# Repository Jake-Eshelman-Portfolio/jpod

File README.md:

# jPod Project Summary

## Goal
A handheld, music-only player about the size of an iPod Video. Stores 32–64GB of music, has a small screen with menus, a 4-way D-pad plus select, Bluetooth headphones, and a wired 3.5mm jack as backup.

## Core design
- **Brain:** ESP32-WROVER (original ESP32). It has classic Bluetooth for headphone audio, Wi-Fi, and 8MB of extra RAM for buffering.
- **Audio:** TI TLV320DAC3100 DAC with a built-in headphone amp, feeding a 3.5mm jack.
- **Storage:** microSD card.
- **Screen:** 2" ST7789 color display.
- **Power:** LiPo battery (1500–2500mAh), USB-C charging, battery-level chip.
- **Software:** Rust on ESP-IDF (`std`). Symphonia handles MP3/FLAC decoding and tags.

## Features
- **Local playback** from the SD card, browsing by artist and album.
- **Streaming** from Navidrome on the Pi over Wi-Fi. Away from home, it reaches the Pi through Tailscale Funnel, protected by a password and a secret token.
- **"Find similar":** pick a song, and the Pi asks Last.fm for similar tracks, then plays any matches from the library or adds the rest to a wishlist.
- **Firmware updates** over Wi-Fi.

## Decisions
- Start with one ESP32. Add a second one for Bluetooth only if streaming over Wi-Fi while playing through Bluetooth stutters.
- Use a 3.5mm jack instead of USB-C headphones.
- Leave LTE for v2, but reserve a spare UART and power header on v1.
- Skip Spotify's API, since it's too locked down now. Use Last.fm instead.

## Plan
1. **Prototype on a breadboard** with a dev kit and breakouts, powered over USB.
2. **Write the software:** playback, UI, Bluetooth, streaming, "find similar".
3. **Design the custom PCB in KiCad** using the same chips.
4. **Order parts.** Separate BOM for schematic based final build and the prototype that will be used to create a test bench.

## Prepare an SD Card (Linux/WSL)
1. Insert the card and inspect disks and partitions:
	```bash
	lsblk -o NAME,PATH,TRAN,RM,SIZE,MODEL,TYPE,FSTYPE,MOUNTPOINTS
	```
2. Identify the removable USB **disk** by model and capacity. Use the whole-disk path (for example, `/dev/sde`), not a partition path such as `/dev/sde1`. The script erases the whole selected disk and creates one MBR/FAT32 partition; Linux sees the USB reader and cannot prove what media is inserted.
3. Ensure `mp3_samples/` contains at least one MP3, then run from the repository root, substituting the verified disk path:
	```bash
	sudo ./helper_scripts/partition_sd_card.sh /dev/sde
	```
4. Check the script's printed model, capacity, and partition list carefully. Continue only if they match the SD card you intend to erase, then type the exact confirmation it requests (device path and size in bytes).

5. To check the music on card:
    - sudo mkdir -p /mnt/jpod-card
    - sudo mount /dev/sde1 /mnt/jpod-card
    - ls /mnt/jpod-card/mp3_samples
    - sudo umount /mnt/jpod-card

The script refuses mounted or otherwise in-use disks. Install its Linux tools if needed with `sudo apt install util-linux fdisk parted dosfstools udev coreutils findutils gawk` (`parted` provides `partprobe`).

## Watch out for
- Wi-Fi and Bluetooth share one radio on the ESP32, so buffer streams aggressively.
- The DAC needs its own 1.8V supply on the custom board.
- The CP2102N USB chip has a long lead time, so buy it early or find a good substitution.

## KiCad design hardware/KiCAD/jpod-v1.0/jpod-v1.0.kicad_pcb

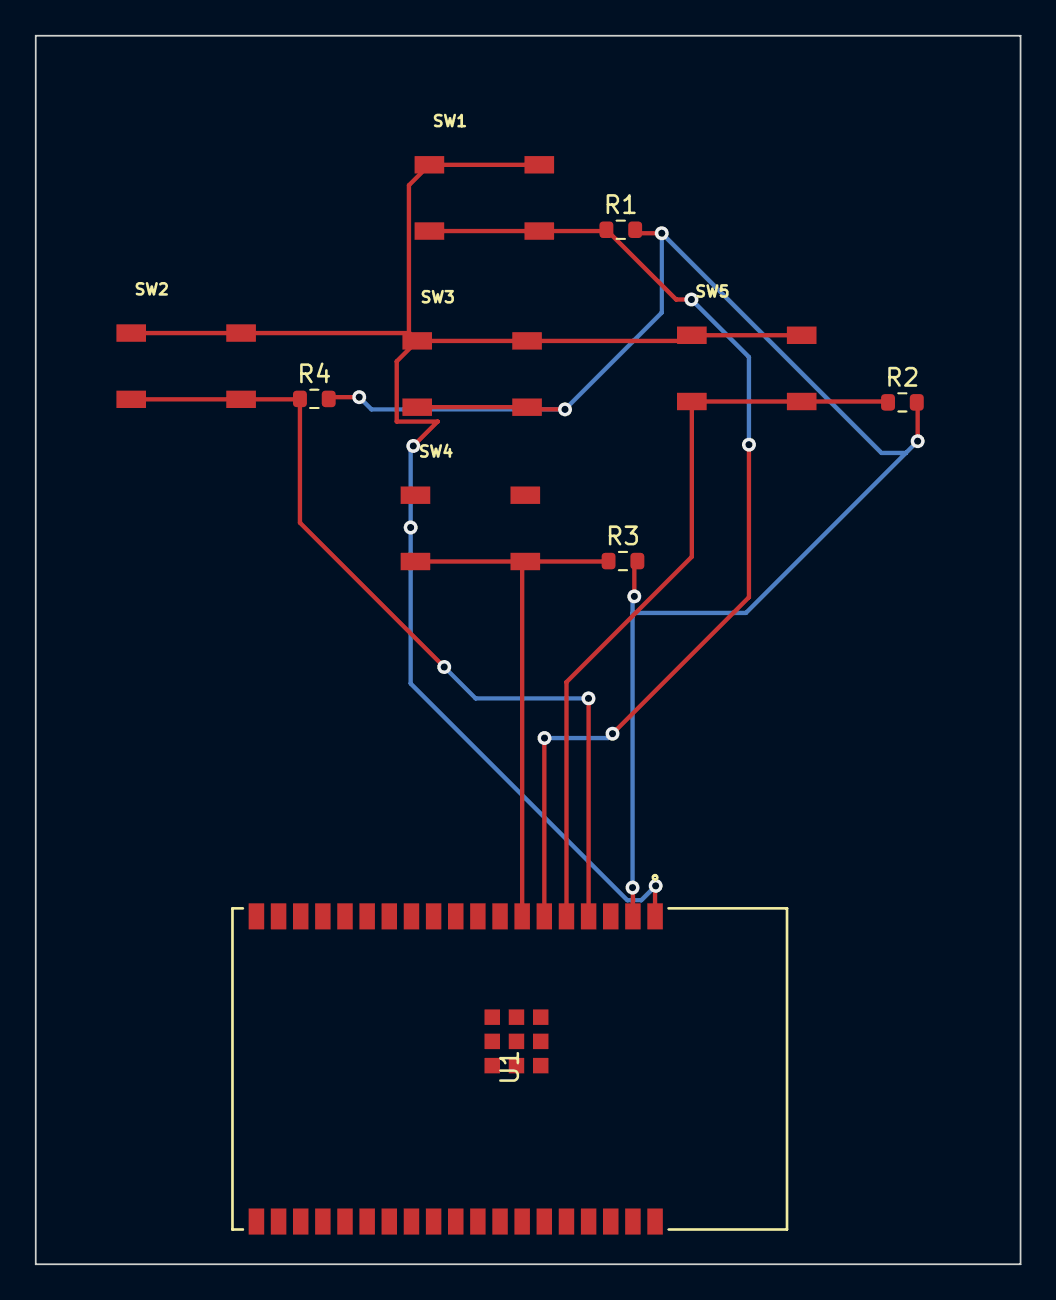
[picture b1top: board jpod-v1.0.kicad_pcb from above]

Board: 2 copper layers, 56.5 x 70.4 mm, 10 parts (0 on the bottom side), 6 nets.

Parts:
R1, R2, R3, R4: 10K; R_0603_1608Metric
SW1, SW2, SW3, SW4, SW5: TL3342F160QG_TR; SW_TL3342F160QG_TR
U1: ESP32-WROVER-E-N16R8; ESP32-WROVER-E_EXP

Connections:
/3V3: R1.2, R2.2, R3.2, R4.2, SW3.1, SW3.2, U1.2 (3V3), U1.8 (IO32)
/GND: SW1.3, SW1.4, SW2.3, SW2.4, SW3.3, SW3.4, SW4.3, SW4.4, SW5.3, SW5.4, U1.1 (GND_2)
/btn_down: R3.1, SW4.1, SW4.2, U1.7 (IO35)
/btn_left: R4.1, SW2.1, SW2.2, U1.4 (SENSOR_VP)
/btn_right: R2.1, SW5.1, SW5.2, U1.5 (SENSOR_VN)
/btn_up: R1.1, SW1.1, SW1.2, U1.6 (IO34)

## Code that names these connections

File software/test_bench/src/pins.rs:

use esp_idf_svc::hal::gpio::{
    Gpio13, Gpio14, Gpio18, Gpio19, Gpio21, Gpio22, Gpio23, Gpio25, Gpio26, Gpio27, Gpio32, Gpio33,
    Gpio34, Gpio35, Gpio36, Gpio39, Gpio4, Gpio5, Pins,
};

// Board pin mappings
pub struct BoardPins {
    pub i2c_sda: Gpio21<'static>,
    pub i2c_scl: Gpio22<'static>,
    pub i2s_bclk: Gpio26<'static>,
    pub i2s_ws: Gpio25<'static>,
    pub i2s_dout: Gpio14<'static>,
    pub spi_sck: Gpio18<'static>,
    pub spi_mosi: Gpio23<'static>,
    pub spi_miso: Gpio19<'static>,
    pub lcd_cs: Gpio5<'static>,
    pub lcd_dc: Gpio27<'static>,
    pub lcd_bl: Gpio4<'static>,
    pub sd_cs: Gpio13<'static>,
    pub btn_up: Gpio34<'static>,
    pub btn_down: Gpio35<'static>,
    pub btn_left: Gpio36<'static>,
    pub btn_right: Gpio39<'static>,
    pub btn_sel: Gpio32<'static>,
    pub hp_detect: Gpio33<'static>,
}

// Init the board pins struct
pub fn board_pins(pins: Pins) -> BoardPins {
    BoardPins {
        i2c_sda: pins.gpio21,
        i2c_scl: pins.gpio22,
        i2s_bclk: pins.gpio26,
        i2s_ws: pins.gpio25,
        i2s_dout: pins.gpio14,
        spi_sck: pins.gpio18,
        spi_mosi: pins.gpio23,
        spi_miso: pins.gpio19,
        lcd_cs: pins.gpio5,
        lcd_dc: pins.gpio27,
        lcd_bl: pins.gpio4,
        sd_cs: pins.gpio13,
        btn_up: pins.gpio34,
        btn_down: pins.gpio35,
        btn_left: pins.gpio36,
        btn_right: pins.gpio39,
        btn_sel: pins.gpio32,
        hp_detect: pins.gpio33,
    }
}

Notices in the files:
parts and their libraries:
COPYRIGHT: Copyright (C) 2025 Ultra Librarian. All rights reserved.
